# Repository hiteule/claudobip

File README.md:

# ClaudoBip

A bunch of electronic cards and software for office automation.

For more information, please read this [blog post].

List of cards :
* [HDMI-CEC] : Drive a TV via the HDMI-CEC protocol.

[blog post]: https://medium.com/blablacar/build-hardware-for-office-automation-34414b0d581a
[HDMI-CEC]:  https://github.com/hiteule/claudobip/tree/master/hdmi-cec

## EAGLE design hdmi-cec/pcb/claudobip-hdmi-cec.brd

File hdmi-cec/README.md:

# ClaudoBip HDMI-CEC

An electronic board designed to drive a TV via the HDMI-CEC protocol.
The instructions are transmitted by radio via a NRF24L01 module.

## PCB

The card must be powered with 5v via the min-usb connector.

The card was designed with [Eagle].
The additional [libraries] used are:
* ATMEGA328P-AU.lbr
* CONNECTORS.lbr
* NRF24L01.lbr
* regulator.lbr

## Software

The firmware turns on the TV when it receives the instruction "workday_start" via the radio and turn it off when it receive the instruction "workday_end".
After turning on the TV it switches to the HDMI2 input automatically. This value is hardcoded.

The HDMI-CEC management is handled by a custom library. You will find the information in the dedicated readme.

The firmware is compiled and uploaded with the Arduino IDE.

The additional libraries used are:
* NRFLite: Handle the radio management. You will found it in the official Arduino repo.
* CEC: Handle the CEC protocol. You will found it in the "libraries" directory.

[Eagle]:     https://www.autodesk.fr/products/eagle
[libraries]: https://github.com/hiteule/eagle-library

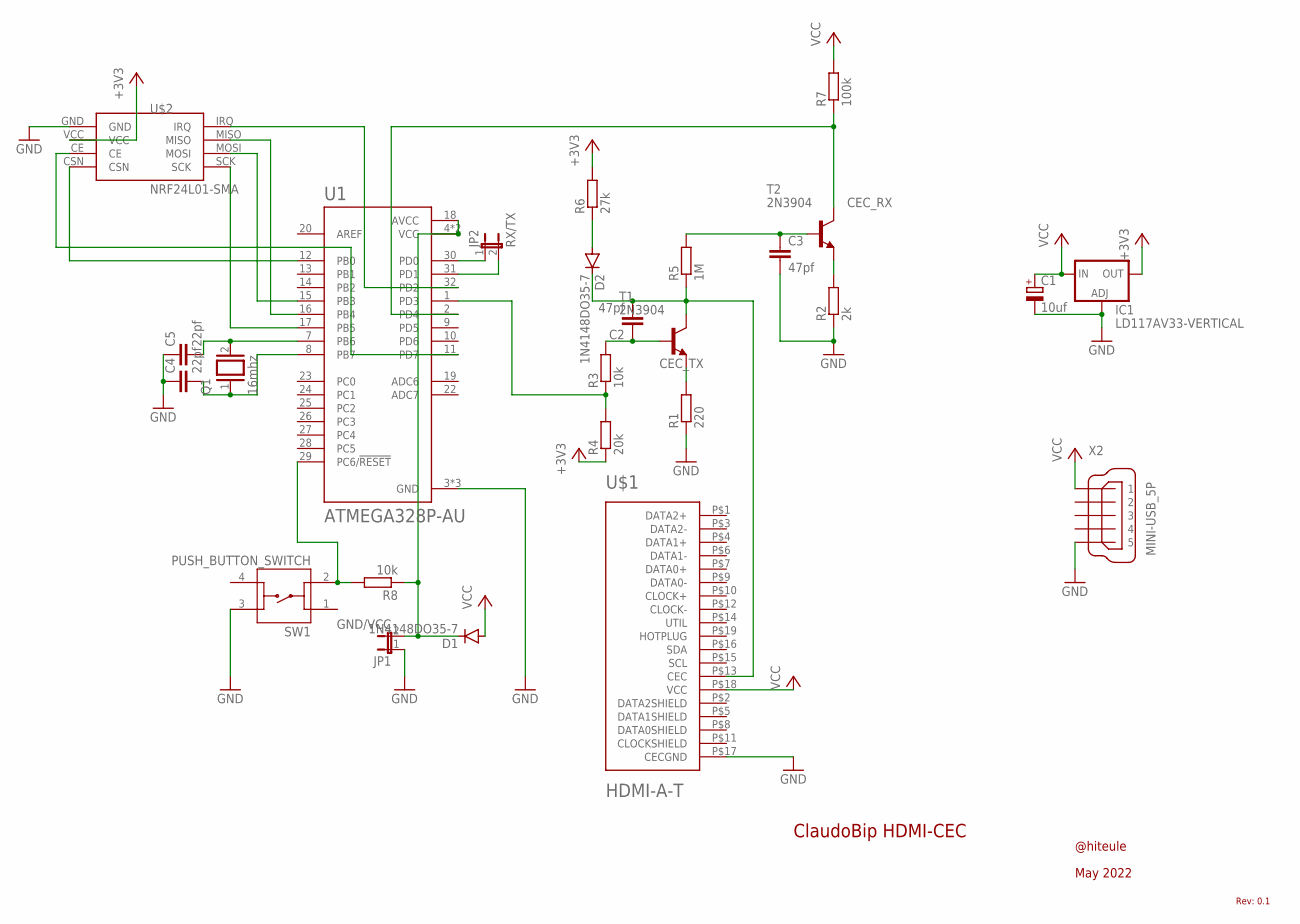
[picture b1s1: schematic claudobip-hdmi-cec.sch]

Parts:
C1: 10uf; E2,5-6E
C2, C3: 47pf; C025-024X044
C4, C5: 22pf; C025-024X044
D1, D2: 1N4148DO35-7; DO35-7
IC1: LD117AV33-VERTICAL; TO220S-VERTICAL
JP1: GND/VCC; JP1
JP2: RX/TX; JP1
Q1: 16mhz; QS
R1: 220; 0204/7
R2: 2k; 0204/7
R3, R8: 10k; 0204/7
R4: 20k; 0204/7
R5: 1M; 0204/7
R6: 27k; 0204/7
R7: 100k; 0204/7
SW1: PUSH_BUTTON_SWITCH
T1, T2: 2N3904; TO92
U1: ATMEGA328P-AU; QFP80P900X900X120-32N
U$1: HDMI-A-T; HDMI_A-T
U$2: NRF24L01-SMA
X2: MINI-USB_5P

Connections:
+3V3: IC1.2 (OUT), R4.1, R6.2, U$2.VCC
CEC_RX: R7.1, T2.1 (C), U1.2 (PD4)
CEC_TX: C2.1, R3.2, T1.2 (B)
GND: C1.-, C3.2, C4.1, C5.1, IC1.1 (ADJ), JP1.1, R1.1, R2.1, SW1.3, U1.3 (GND), U1.5 (GND), U1.21 (GND), U$1.P$17 (CECGND), U$2.GND, X2.5
unnamed: R1.2, T1.3 (E)
unnamed: C5.2, Q1.2, U1.7 (PB6)
unnamed: C4.2, Q1.1, U1.8 (PB7)
unnamed: R8.2, SW1.2, U1.29 (PC6/!RESET)
unnamed: D1.C, JP1.2, R8.1, U1.4 (VCC), U1.6 (VCC), U1.18 (AVCC)
unnamed: U1.16 (PB4), U$2.MISO
unnamed: U1.15 (PB3), U$2.MOSI
unnamed: U1.12 (PB0), U$2.CSN
unnamed: U1.11 (PD7), U$2.CE
unnamed: U1.32 (PD2), U$2.IRQ
unnamed: U1.17 (PB5), U$2.SCK
unnamed: JP2.1, U1.30 (PD0)
unnamed: JP2.2, U1.31 (PD1)
unnamed: R2.2, T2.3 (E)
unnamed: C3.1, R5.2, T2.2 (B)
unnamed: R3.1, R4.2, U1.1 (PD3)
unnamed: C2.2, D2.C, R5.1, T1.1 (C), U$1.P$13 (CEC)
unnamed: D2.A, R6.1
VCC: C1.+, D1.A, IC1.3 (IN), R7.2, U$1.P$18 (VCC), X2.1

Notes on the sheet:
Rev: 0.1
May 2022
@hiteule
ClaudoBip HDMI-CEC

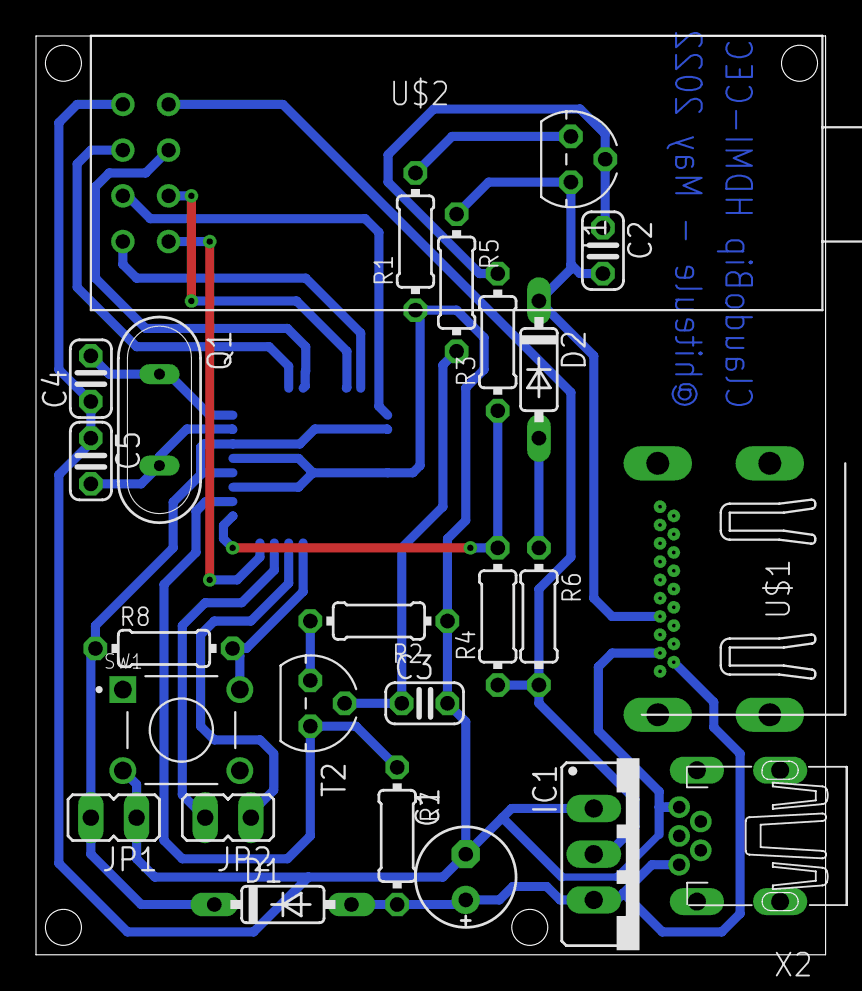
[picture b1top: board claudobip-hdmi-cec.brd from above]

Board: 2 copper layers, 43.9 x 51.0 mm, 26 parts (1 on the bottom side), 23 nets.

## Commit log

2022-05-08 [HDMI-CEC] Add pcb schematic & board
2022-05-08 Add readme
2022-06-19 [HDMI-CEC] Use a vertical footprint for the LD117AV33 regulator
2022-07-31 Add software
